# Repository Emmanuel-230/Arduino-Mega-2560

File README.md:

# Arduino-Mega-2560
Arduino Mega 2560 PCB Design

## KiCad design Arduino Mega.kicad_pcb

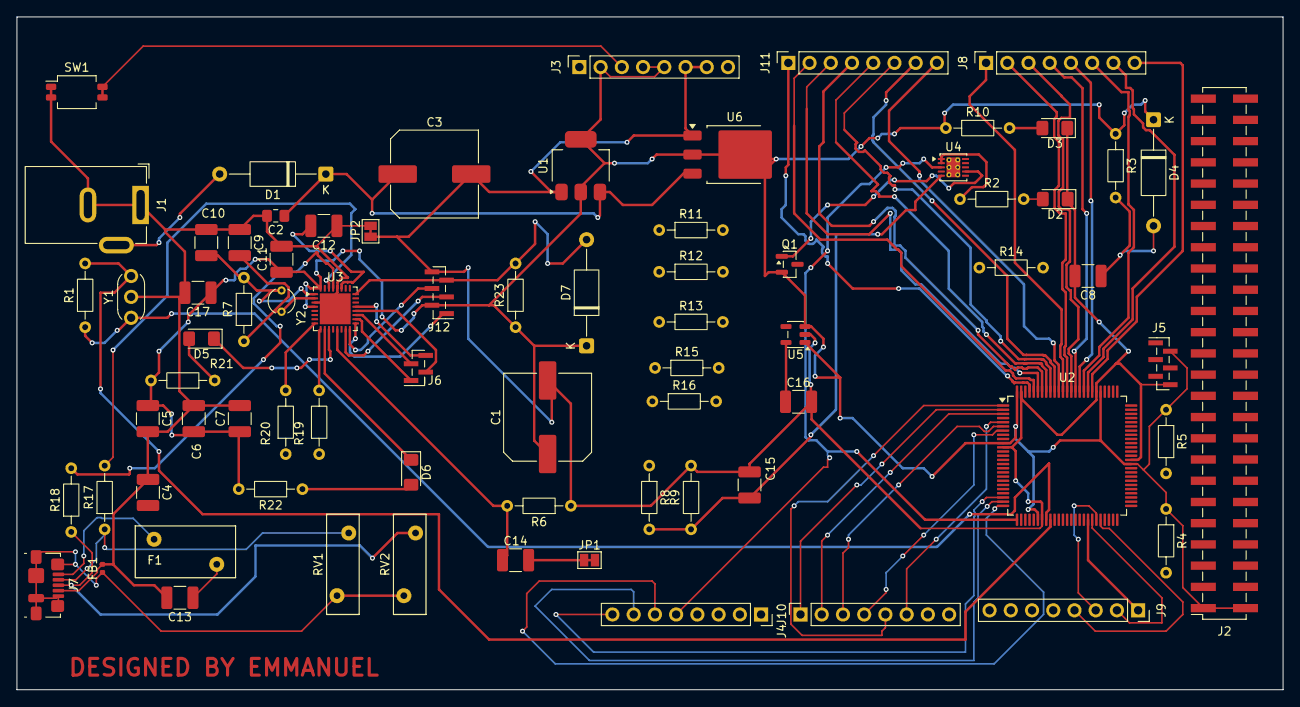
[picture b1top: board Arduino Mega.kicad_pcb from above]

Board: 2 copper layers, 151.5 x 80.5 mm, 75 parts (0 on the bottom side), 66 nets.

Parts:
C1, C3: C_Polarized; C_Elec_10x10.2
C2: C; C_0805_2012Metric_Pad1.18x1.45mm_HandSolder
C4, C5, C6, C7, C8, C9, C10, C11, C12, C13, C14, C15, C16, C17: C; C_1210_3225Metric_Pad1.33x2.70mm_HandSolder
D1, D4, D7: D; D_A-405_P12.70mm_Horizontal
D2, D3, D5, D6: LED; LED_1206_3216Metric_Pad1.42x1.75mm_HandSolder
F1: Polyfuse; RV_Disc_D12mm_W6.2mm_P7.5mm
FB1: FerriteBead; L_0402_1005Metric
J1: Barrel_Jack_Switch; BarrelJack_GCT_DCJ200-10-A_Horizontal
J2: Conn_02x18_Odd_Even; PinSocket_2x25_P2.54mm_Vertical_SMD
J3, J8, J9, J10, J11: Conn_01x08; PinSocket_1x08_P2.54mm_Vertical
J4: Conn_01x10; PinSocket_1x08_P2.54mm_Vertical
J5, J12: Conn_02x03_Odd_Even; PinHeader_1x06_P1.00mm_Vertical_SMD_Pin1Left
J6: Conn_02x02_Odd_Even; PinHeader_1x04_P1.00mm_Vertical_SMD_Pin1Right
J7: USB_B_Micro; USB_Micro-B_Molex_47346-0001
JP1, JP2: SolderJumper_2_Open; SolderJumper-2_P1.3mm_Open_Pad1.0x1.5mm
Q1: FDN340P; SOT-23
R1, R2, R3, R4, R5, R6, R7, R8, R9, R10, R11, R12, R13, R14, R15, R16, R17, R18, R19, R20, R21, R22, R23: R; R_Axial_DIN0204_L3.6mm_D1.6mm_P7.62mm_Horizontal
RV1, RV2: Varistor; RV_Disc_D12mm_W3.9mm_P7.5mm
SW1: SW_MEC_5E; SW_DIP_SPSTx02_Slide_Omron_A6H-2101_W6.15mm_P1.27mm
U1: NCP1117-5.0_SOT223; SOT-223-3_TabPin2
U2: ATmega2560-16A; TQFP-100_14x14mm_P0.5mm
U3: ATmega16U2-M; QFN-32-1EP_5x5mm_P0.5mm_EP3.7x3.7mm
U4: LMV358; LFCSP-WD-10-1EP_3x3mm_P0.5mm_EP1.64x2.38mm_ThermalVias
U5: LP2985-3.3; SOT-23-5
U6: AMS1117CD-5.0; TO-252-3_TabPin2
Y1: Resonator; Resonator-3Pin_W6.0mm_H3.0mm
Y2: Crystal; Crystal_AT310_D3.0mm_L10.0mm_Vertical

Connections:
+5V: C1.1, C5.1, C6.1, C7.1, C11.1, C17.1, D4.1 (K_1), D7.1 (K), J2.1, J2.2, J3.2, J3.4, J3.5, J5.2, J12.2, Q1.2 (S), R3.1, R4.1, R5.1, R10.1, R21.2, R22.2, R23.1, U1.2 (VO), U2.10 (VCC), U2.31 (VCC), U2.61 (VCC), U2.80 (VCC), U2.100 (AVCC), U3.4 (VCC), U3.32 (AVCC), U5.1 (VIN), U5.3 (ON/~OFF), U6.2 (VO)
GNDD: C1.2, C2.2, C3.2, C4.1, C5.2, C6.2, C7.2, C8.2, C9.1, C10.1, C11.2, C12.1, C13.2, C15.2, C16.2, C17.2, D2.1 (K), D3.1 (K), FB1.2, J1.1, J1.2, J3.6, J3.7, J5.6, J7.4 (ID), J12.6, JP2.1 (A), JP2.2 (B), R6.1, R9.2, SW1.1, SW1.2, U1.1 (GND), U2.11 (GND), U2.32 (GND), U2.62 (GND), U2.81 (GND), U2.99 (GND), U3.3 (GND), U3.28 (UGND), U3.33 (GND), U5.2 (GND), U6.1 (GND), Y1.2
unnamed: D1.2 (A), J1.3
unnamed: C2.1, C3.1, D1.1 (K), U1.3 (VI), U6.3 (VI)
unnamed: D2.2 (A), R2.2
unnamed: D3.2 (A), R10.2
unnamed: D5.2 (A), R21.1
unnamed: D5.1 (K), U3.11 (PD5)
unnamed: D6.2 (A), R22.1
unnamed: D6.1 (K), U3.10 (PD4)
unnamed: D7.2 (A), J12.5, R23.2, U3.24 (PC1/~RESET)
unnamed: J3.3, SW1.3 (K), SW1.4 (A)
unnamed: J4.5, U2.26 (PB7), U4.3 (+)
unnamed: J4.6, U2.25 (PB6)
unnamed: J4.7, U2.24 (PB5)
unnamed: J4.8, U2.23 (PB4)
unnamed: J6.1, U3.18 (PB4)
unnamed: J6.2, U3.20 (PB6)
unnamed: J6.3, U3.19 (PB5)
unnamed: J6.4, U3.21 (PB7)
unnamed: J7.3 (D+), R18.1, RV2.1
unnamed: J7.2 (D-), R17.1, RV1.1
unnamed: FB1.1, J7.5 (GND), J7.SH (Shield), RV1.2, RV2.2
unnamed: F1.1, J7.1 (VBUS)
unnamed: J8.1, U2.89 (PK0)
unnamed: J8.2, U2.88 (PK1)
unnamed: J8.3, U2.87 (PK2)
unnamed: J8.4, U2.86 (PK3)
unnamed: J8.5, U2.85 (PK4)
unnamed: J8.6, U2.84 (PK5)
unnamed: J8.7, U2.83 (PK6)
unnamed: J8.8, U2.82 (PK7)
unnamed: J9.1, U2.43 (PD0)
unnamed: J9.2, U2.44 (PD1)
unnamed: J9.3, U2.45 (PD2)
unnamed: J9.4, U2.46 (PD3)
unnamed: J10.1, U2.2 (PE0)
unnamed: J10.2, U2.3 (PE1)
unnamed: J10.3, U2.6 (PE4)
unnamed: J10.4, U2.7 (PE5)
unnamed: J10.5, U2.1 (PG5)
unnamed: J10.6, U2.5 (PE3)
unnamed: J11.1, U2.97 (PF0)
unnamed: J11.2, U2.96 (PF1)
unnamed: J11.3, U2.95 (PF2)
unnamed: J11.4, U2.94 (PF3)
unnamed: J11.5, U2.93 (PF4)
unnamed: J11.6, U2.92 (PF5)
unnamed: J11.7, U2.91 (PF6)
unnamed: J11.8, U2.90 (PF7)
unnamed: J12.1, U3.17 (PB3)
unnamed: J12.3, U3.15 (PB1)
unnamed: J12.4, U3.16 (PB2)
unnamed: Q1.1 (G), U4.7
unnamed: R1.2, U2.34 (XTAL1), Y1.3
unnamed: R1.1, U2.33 (XTAL2), Y1.1
unnamed: R18.2, U3.29 (D+)
unnamed: R17.2, U3.30 (D-)
unnamed: C9.2, R7.1, U3.2 (PC0/XTAL2), Y2.2
unnamed: R20.2, U3.8 (PD2)
unnamed: R19.2, U3.9 (PD3)
unnamed: C12.2, U3.27 (UCAP)
unnamed: C10.2, R7.2, U3.1 (XTAL1), Y2.1
unnamed: C14.1, R6.2, U3.13 (~HWB/PD7)
unnamed: R2.1, U4.1, U4.2 (-)
unnamed: C15.1, R8.2, R9.1, U4.5 (+)
